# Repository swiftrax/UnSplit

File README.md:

# UnSplit
A Kyria layout with some of the thumb keys removed. It is non split and powered by an ATMega32u4-AU. Featuring an exposed component layout with diodes in a bank.

## PCB Renders
Top Full Ground Plane

Bottom Full Ground Plane

Top Partial Ground Plane

Bottom Partial Ground Plane

*Open with KiCad nightly*

## Bill of Materials
* [ATMega32u4-AU x 1](https://lcsc.com/product-detail/ATMEL-AVR_Microchip-Tech-ATMEGA32U4-AU_C44854.html)
* [16MHz Resonator x 1](https://lcsc.com/product-detail/Others_Murata-Electronics-CSTNE16M0V530000R0_C341521.html)
* [22 Ohm Resistor x 2](https://lcsc.com/product-detail/Chip-Resistor-Surface-Mount_TyoHM-RMC0805221-N_C325772.html)
* [5.1k Ohm Resistor x 2](https://lcsc.com/product-detail/Chip-Resistor-Surface-Mount_TyoHM-RMC08055-1K1-N_C269748.html)
* [10k Ohm Resistor x 2](https://lcsc.com/product-detail/Chip-Resistor-Surface-Mount_TyoHM-RMC080510K1-N_C269742.html)
* [100nF Capactior x 3](https://lcsc.com/product-detail/Multilayer-Ceramic-Capacitors-MLCC-SMD-SMT_Walsin-Tech-Corp-0805B104J500CT_C314285.html)
* [1uF Capactior x 1](https://lcsc.com/product-detail/Multilayer-Ceramic-Capacitors-MLCC-SMD-SMT_FH-Guangdong-Fenghua-Advanced-Tech-0805B105K500NT_C215803.html)
* [10uF Capactior x 1](https://lcsc.com/product-detail/Multilayer-Ceramic-Capacitors-MLCC-SMD-SMT_SAMSUNG_CL10A106MA8NRNC_10uF-106-20-25V_C96446.html)
* [500mA Polyfuse x 1](https://lcsc.com/product-detail/Surface-Mount-Fuses_0-25A-16V-Self-healing-fuse_C70068.html)
* [Reset Switch x 1](https://lcsc.com/product-detail/Tactile-Switches_C-K_RS-187R05A2-DSMTRT_C-K-RS-187R05A2-DSMTRT_C221929.html)
* [Type C Port x 1](https://lcsc.com/product-detail/USB-Type-C_Korean-Hroparts-Elec-TYPE-C-31-M-14_C223907.html)
* [Diodes x 44](https://lcsc.com/product-detail/Diodes-General-Purpose_MDD-Microdiode-Electronics-SM4007PL_C64898.html)

*Capactiors and Resistors are 0805 Package size*

## License

This repository is under the [GNU GPL V2 license](https://github.com/swiftrax/UnSplit/blob/master/LICENSE). If you plan to sell these pcbs, make sure to read it.

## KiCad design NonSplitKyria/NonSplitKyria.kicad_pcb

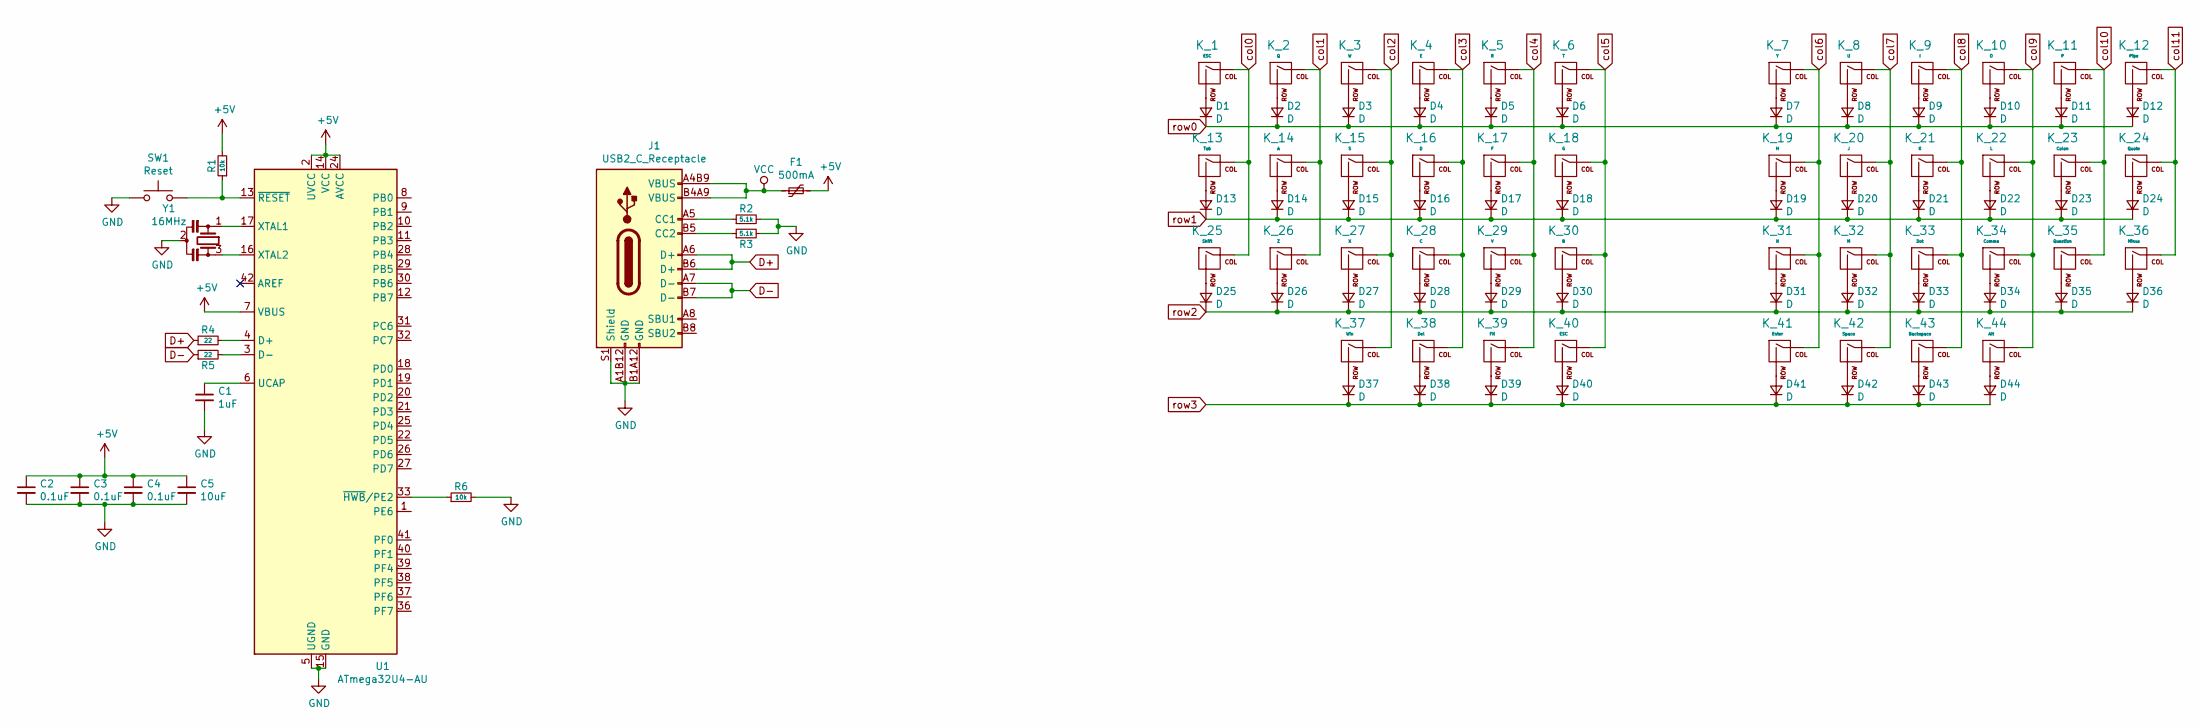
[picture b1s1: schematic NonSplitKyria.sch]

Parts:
C1: 1uF; C_0805_2012Metric
C2, C3, C4: 0.1uF; C_0805_2012Metric
C5: 10uF; C_0805_2012Metric
D1, D2, D3, D4, D5, D6, D7, D8, D9, D10, D11, D12, D13, D14, D15, D16, D17, D18, D19, D20, D21, D22, D23, D24, D25, D26, D27, D28, D29, D30, D31, D32, D33, D34, D35, D36, D37, D38, D39, D40, D41, D42, D43, D44: D; D_SOD-123
F1: 500mA; Fuse_1206_3216Metric
J1: USB2_C_Receptacle; Mid_Mount-USB_C_HandSoldering
K_1, K_40: ESC; MXOnly-1U-NoLED
K_2: Q; MXOnly-1U-NoLED
K_3: W; MXOnly-1U-NoLED
K_4: E; MXOnly-1U-NoLED
K_5: R; MXOnly-1U-NoLED
K_6: T; MXOnly-1U-NoLED
K_7: Y; MXOnly-1U-NoLED
K_8: U; MXOnly-1U-NoLED
K_9: I; MXOnly-1U-NoLED
K_10: O; MXOnly-1U-NoLED
K_11: P; MXOnly-1U-NoLED
K_12: Pipe; MXOnly-1U-NoLED
K_13: Tab; MXOnly-1U-NoLED
K_14: A; MXOnly-1U-NoLED
K_15: S; MXOnly-1U-NoLED
K_16: D; MXOnly-1U-NoLED
K_17: F; MXOnly-1U-NoLED
K_18: G; MXOnly-1U-NoLED
K_19: H; MXOnly-1U-NoLED
K_20: J; MXOnly-1U-NoLED
K_21: K; MXOnly-1U-NoLED
K_22: L; MXOnly-1U-NoLED
K_23: Colon; MXOnly-1U-NoLED
K_24: Quote; MXOnly-1U-NoLED
K_25: Shift; MXOnly-1U-NoLED
K_26: Z; MXOnly-1U-NoLED
K_27: X; MXOnly-1U-NoLED
K_28: C; MXOnly-1U-NoLED
K_29: V; MXOnly-1U-NoLED
K_30: B; MXOnly-1U-NoLED
K_31: N; MXOnly-1U-NoLED
K_32: M; MXOnly-1U-NoLED
K_33: Dot; MXOnly-1U-NoLED
K_34: Comma; MXOnly-1U-NoLED
K_35: Question; MXOnly-1U-NoLED
K_36: Minus; MXOnly-1U-NoLED
K_37: Win; MXOnly-1U-NoLED
K_38: Del; MXOnly-1U-NoLED
K_39: FN; MXOnly-1U-NoLED
K_41: Enter; MXOnly-1U-NoLED
K_42: Space; MXOnly-1U-NoLED
K_43: Backspace; MXOnly-1U-NoLED
K_44: Alt; MXOnly-1U-NoLED
R1, R6: 10k; R_0805_2012Metric
R2, R3: 5.1k; R_0805_2012Metric
R4, R5: 22; R_0805_2012Metric
SW1: Reset; SKQG-1155865
U1: ATmega32U4-AU; TQFP-44_10x10mm_P0.8mm
Y1: 16MHz; Resonator_SMD_muRata_CSTxExxV-3Pin_3.0x1.1mm_HandSoldering_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

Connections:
+5V: C2.1, C3.1, C4.1, C5.1, F1.2, R1.2, U1.2 (UVCC), U1.7 (VBUS), U1.14 (VCC), U1.24 (AVCC), U1.34 (VCC), U1.44 (AVCC)
D+: J1.A6 (D+), J1.B6 (D+), R4.1
D-: J1.A7 (D-), J1.B7 (D-), R5.1
GND: C1.2, C2.2, C3.2, C4.2, C5.2, J1.A1B12 (GND), J1.B1A12 (GND), J1.S1 (Shield), R2.2, R3.2, R6.2, SW1.1, U1.5 (UGND), U1.15 (GND), U1.23 (GND), U1.35 (GND), U1.43 (GND), Y1.2
unnamed: C1.1, U1.6 (UCAP)
unnamed: D1.2 (A), K_1.2 (ROW)
unnamed: D2.2 (A), K_2.2 (ROW)
unnamed: D3.2 (A), K_3.2 (ROW)
unnamed: D4.2 (A), K_4.2 (ROW)
unnamed: D5.2 (A), K_5.2 (ROW)
unnamed: D6.2 (A), K_6.2 (ROW)
unnamed: D7.2 (A), K_7.2 (ROW)
unnamed: D8.2 (A), K_8.2 (ROW)
unnamed: D9.2 (A), K_9.2 (ROW)
unnamed: D10.2 (A), K_10.2 (ROW)
unnamed: D11.2 (A), K_11.2 (ROW)
unnamed: D12.2 (A), K_12.2 (ROW)
unnamed: D13.2 (A), K_13.2 (ROW)
unnamed: D14.2 (A), K_14.2 (ROW)
unnamed: D15.2 (A), K_15.2 (ROW)
unnamed: D16.2 (A), K_16.2 (ROW)
unnamed: D17.2 (A), K_17.2 (ROW)
unnamed: D18.2 (A), K_18.2 (ROW)
unnamed: D19.2 (A), K_19.2 (ROW)
unnamed: D20.2 (A), K_20.2 (ROW)
unnamed: D21.2 (A), K_21.2 (ROW)
unnamed: D22.2 (A), K_22.2 (ROW)
unnamed: D23.2 (A), K_23.2 (ROW)
unnamed: D24.2 (A), K_24.2 (ROW)
unnamed: D25.2 (A), K_25.2 (ROW)
unnamed: D26.2 (A), K_26.2 (ROW)
unnamed: D27.2 (A), K_27.2 (ROW)
unnamed: D28.2 (A), K_28.2 (ROW)
unnamed: D29.2 (A), K_29.2 (ROW)
unnamed: D30.2 (A), K_30.2 (ROW)
unnamed: D31.2 (A), K_31.2 (ROW)
unnamed: D32.2 (A), K_32.2 (ROW)
unnamed: D33.2 (A), K_33.2 (ROW)
unnamed: D34.2 (A), K_34.2 (ROW)
unnamed: D35.2 (A), K_35.2 (ROW)
unnamed: D36.2 (A), K_36.2 (ROW)
unnamed: D37.2 (A), K_37.2 (ROW)
unnamed: D38.2 (A), K_38.2 (ROW)
unnamed: D39.2 (A), K_39.2 (ROW)
unnamed: D40.2 (A), K_40.2 (ROW)
unnamed: D41.2 (A), K_41.2 (ROW)
unnamed: D42.2 (A), K_42.2 (ROW)
unnamed: D43.2 (A), K_43.2 (ROW)
unnamed: D44.2 (A), K_44.2 (ROW)
unnamed: J1.A5 (CC1), R2.1
unnamed: J1.B5 (CC2), R3.1
unnamed: R1.1, SW1.2, U1.13 (~RESET)
unnamed: R4.2, U1.4 (D+)
unnamed: R5.2, U1.3 (D-)
unnamed: R6.1, U1.33 (~HWB~/PE2)
unnamed: U1.16 (XTAL2), Y1.3
unnamed: U1.17 (XTAL1), Y1.1
VCC: F1.1, J1.A4B9 (VBUS), J1.B4A9 (VBUS)
col0: K_1.1 (COL), K_13.1 (COL), K_25.1 (COL), U1.19 (PD1)
col1: K_2.1 (COL), K_14.1 (COL), K_26.1 (COL), U1.20 (PD2)
col2: K_3.1 (COL), K_15.1 (COL), K_27.1 (COL), K_37.1 (COL), U1.21 (PD3)
col3: K_4.1 (COL), K_16.1 (COL), K_28.1 (COL), K_38.1 (COL), U1.22 (PD5)
col4: K_5.1 (COL), K_17.1 (COL), K_29.1 (COL), K_39.1 (COL), U1.25 (PD4)
col5: K_6.1 (COL), K_18.1 (COL), K_30.1 (COL), K_40.1 (COL), U1.26 (PD6)
col6: K_7.1 (COL), K_19.1 (COL), K_31.1 (COL), K_41.1 (COL), U1.31 (PC6)
col7: K_8.1 (COL), K_20.1 (COL), K_32.1 (COL), K_42.1 (COL), U1.32 (PC7)
col8: K_9.1 (COL), K_21.1 (COL), K_33.1 (COL), K_43.1 (COL), U1.37 (PF6)
col9: K_10.1 (COL), K_22.1 (COL), K_34.1 (COL), K_44.1 (COL), U1.38 (PF5)
col10: K_11.1 (COL), K_23.1 (COL), K_35.1 (COL), U1.39 (PF4)
col11: K_12.1 (COL), K_24.1 (COL), K_36.1 (COL), U1.40 (PF1)
row0: D1.1 (K), D2.1 (K), D3.1 (K), D4.1 (K), D5.1 (K), D6.1 (K), D7.1 (K), D8.1 (K), D9.1 (K), D10.1 (K), D11.1 (K), D12.1 (K), U1.30 (PB6)
row1: D13.1 (K), D14.1 (K), D15.1 (K), D16.1 (K), D17.1 (K), D18.1 (K), D19.1 (K), D20.1 (K), D21.1 (K), D22.1 (K), D23.1 (K), D24.1 (K), U1.27 (PD7)
row2: D25.1 (K), D26.1 (K), D27.1 (K), D28.1 (K), D29.1 (K), D30.1 (K), D31.1 (K), D32.1 (K), D33.1 (K), D34.1 (K), D35.1 (K), D36.1 (K), U1.29 (PB5)
row3: D37.1 (K), D38.1 (K), D39.1 (K), D40.1 (K), D41.1 (K), D42.1 (K), D43.1 (K), D44.1 (K), U1.28 (PB4)

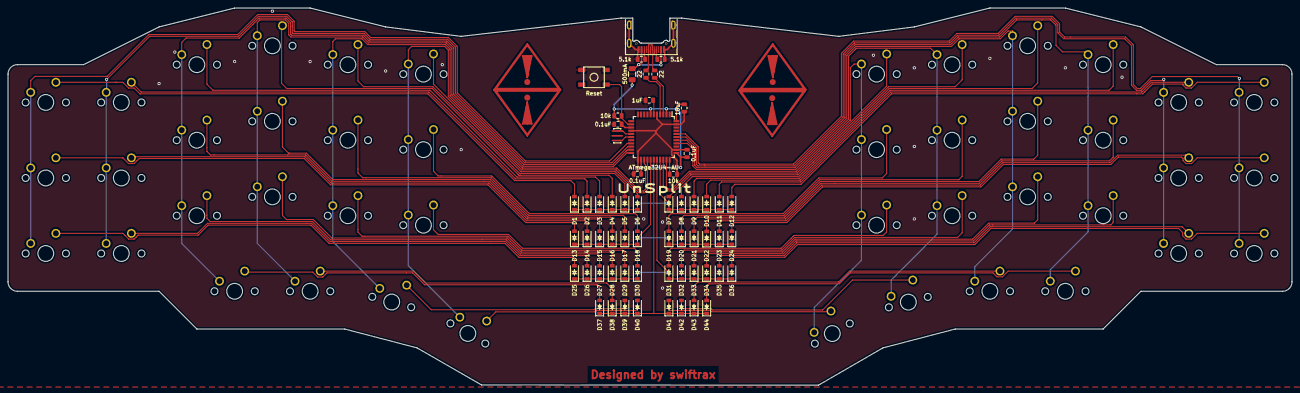
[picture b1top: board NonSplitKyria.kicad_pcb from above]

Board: 2 copper layers, 323.8 x 95.0 mm, 104 parts (0 on the bottom side), 74 nets.

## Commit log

2020-06-03 Route Diodes
2020-06-04 Route MCU rows + cols
2020-06-04 Add Silkscreen art
2020-06-04 Add Gerbers
2020-06-04 Redo Gerbers
2020-06-04 Add PCB Renders
2020-06-04 Create LICENSE
2020-06-04 Green PCB render
2020-06-04 Add plates
2020-06-05 Organize Files
2020-06-05 Add Purple PCB Renders
2020-06-05 Add Minimal GND plane images
2020-07-09 Add BOM
